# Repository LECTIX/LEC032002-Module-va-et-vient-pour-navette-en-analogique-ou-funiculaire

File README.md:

# LEC032002 - Module va et vient pour navette en analogique ou funiculaire
Fichiers sources pour le produit LEC032002

## Description du produit

- **AUTOMATIQUE** gérez votre train en mode navette ou votre funiculaire automatiquement
- **ACCÉLÉRATION** et freinage progressifs
- **TEMPORISATION** réglable entre 1 s et plus de 3 min
- **SIMPLICITÉ** Réglage facile de la vitesse maximum, du temps d'arrêt, de la courbe d'accélération et de freinage
- **SÉCURITÉ** Protection contre les courts circuits

## Utiliser les fichiers sources pour fabriquer le produit

Il n'est **pas nécessaire de savoir souder ou d'être bon en électronique** pour se procurer ce produit. Grâce aux fichiers sources publiés ici, vous pouvez être en mesure de faire fabriquer ce produit par un sous traitant.

**ATTENTION** ce produit nécessite une programmation afin de pouvoir fonctionner. Vous devez pour cela posséder le programmateur et programmer vous même la carte. Cette étape peut nécessiter des connaissances techniques, si nécessaire, nous vous encourrageons à vous rapprocher d'un club.

### Faire fabriquer chez un sous traitant

Il est aujourd'hui possible de faire fabriquer à moindre cout des cartes électroniques. Nous recommendons [JLCPCB](https://jlcpcb.com/) si vous voulez aller au moins cher. Si vous préférez un acteur européen, [eurocircuits](https://www.eurocircuits.com/) est un des acteurs reconnus.

1. Télécherger les sources de ce produit en cliquant sur le bouton `Code`, puis `Download ZIP`.
1. Décompresser le dossier.
1. Les fichiers pour la fabrication se trouvent dans le répertoire `hardware/prod`.
1. Se connecter sur [https://cart.jlcpcb.com/quote](https://cart.jlcpcb.com/quote)
1. Cliquer sur le bouton `Add gerber file` et sélectionner le fichier `gerbers.zip`.
1. Sélectionnez la quantité de cartes que vous souhaitez dans le champs `PCB Qty`.
1. Laisser toutes les autres options par défaut, puis cliquez sur le toggle switch en face de `PCB Assembly`, et enfin sur le bouton `confirm`.
1. Une preview de la carte électronique sans les composants doit apparaitre. Cliquez sur `NEXT`.
1. Cliquez sur le bouton `Add BOM File`, puis sélectionnez le fichier `bom.csv`
1. Cliquez sur le bouton `Add CPL File`, puis sélectionnez le fichier `pos.csv`
1. **Vérifier que tous les composants sont en stock** et bien sélectionnés, puis cliquez sur `NEXT`.
1. Une preview de la carte avec ses composants apparait. Continuer le chemin en cliquant sur `NEXT`.
1. Le prix final apparait. Sélectionnez la catégorie du produit, puis cliquez sur `SAVE TO CART`.
1. Une fois sauvegardé dans votre panier, vous pouvez valider votre commande et choisir le moyen d'acheminement. Afin de ne pas avoir à se préoccuper des frais de douane, nous vous conseillons de choisir une méthode d'expédition DDP.

Vous receverez vos cartes sous 1 à 3 semaines. 

**Nous ne sommes en aucun cas responsables des cartes qui arriveraient défectueuses ou non fonctionnelles.**

### Modifications des fichiers sources

Installez kicad 6 (ou version supérieure), et ouvrez le fichier LEC032002.kicad_pro

### Programation

Pour programmer le module, vous devez posséder
- un programmateur AVR type USBASP
- une sonde Tag-Connect TC2050

Le firmware se trouve dans le dossier du même nom. Il est recommandé d'utiliser VS-code et platform-io pour programmer la carte. Pour ce faire, branchez le programmateur à votre PC et à la carte à programmer, puis rentrer les commandes suivantes :

```
cd firmware
platformio run --target fuses && platformio run --target upload
```

### Regénérer les fichiers gerber, BOM, et position (Optionnel)

Peut se faire simplement en utilisant kikit :

```
cd hardware
docker run --rm -w /kikit -v $PWD:/kikit yaqwsx/kikit kikit fab jlcpcb --assembly --no-drc --schematic LEC032002.kicad_sch --field LCSC --corrections JLCPCB_CORRECTION --nametemplate LEC032002_{} LEC032002.kicad_pcb prod/

```
## Notices
[Manuel FR](docs/manual_fr.pdf)

## License
Tous nos fichiers sont plubliés sous les licenses
- CERN Open Hardware Licence Version 2 - Strongly Reciprocal pour ce qui touche au hardware
- GNU General Public License v3.0 pour tout ce qui est software

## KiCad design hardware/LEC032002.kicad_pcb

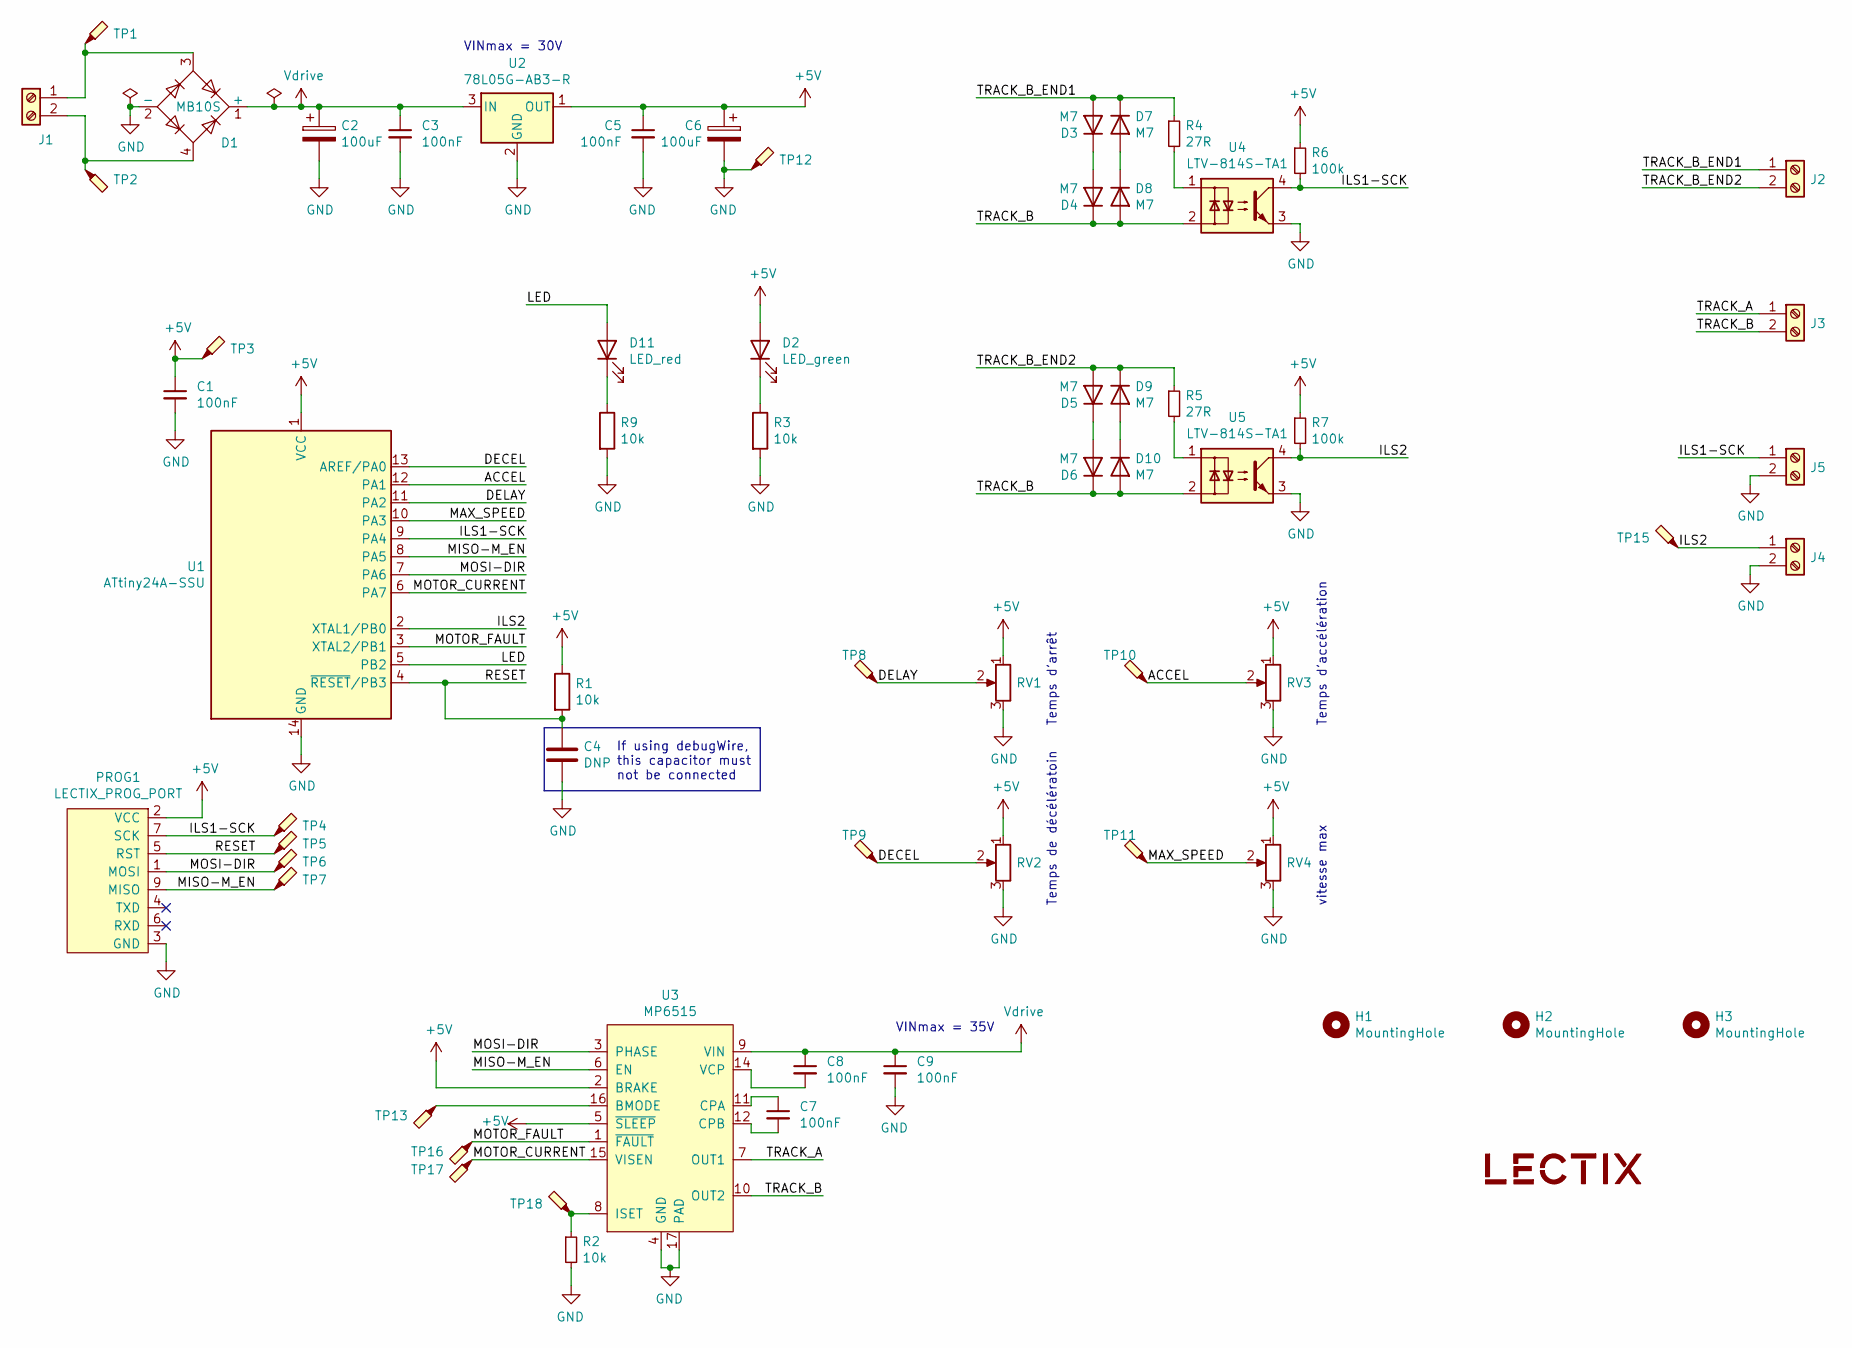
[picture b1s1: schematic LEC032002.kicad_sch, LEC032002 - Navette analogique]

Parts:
C1, C3, C5, C7, C8, C9: 100nF; C_0603_1608Metric; LCSC C14663
C2, C6: 100uF; CP_Elec_6.3x7.7; LCSC C249982
C4: DNP; C_0603_1608Metric; LCSC DNP
D1: MB10S; TO-269AA; LCSC C2488
D2: LED_green; LED_0603_1608Metric; MPN 19-217/GHC-YR1S2/3T; LCSC C72043
D3, D4, D5, D6, D7, D8, D9, D10: M7; D_SMA; MPN M7; LCSC C95872
D11: LED_red; LED_0603_1608Metric; LCSC C2286
H1, H2, H3: MountingHole; MountingHole_3.2mm_M3; LCSC DNP
J1: Screw_Terminal_01x02_green; TerminalBlock_bornier-2_P5.08mm-green; MPN DB126V-5.0-2P-GN; LCSC C395849
J2, J3, J4, J5: Screw_Terminal_01x02_blue; TerminalBlock_bornier-2_P5.08mm-blue; MPN DB301V-5.0-2P-BU-P; LCSC C430621
LOGO1: logo_lectix_25mm; Logo_10mm; LCSC DNP
PROG1: LECTIX_PROG_PORT; Tag-Connect_TC2050-IDC-FP_2x05_P1.27mm_Vertical; LCSC DNP
R1, R2, R3, R9: 10k; R_0603_1608Metric; LCSC C25804
R4, R5: 27R; R_0603_1608Metric; LCSC C25190
R6, R7: 100k; R_0603_1608Metric; LCSC C25803
RV1, RV2, RV3, RV4: pot_smd_100k_3362P; BOURNS-3362P_pot; MPN 3362P-1-104; LCSC C118966
TP1, TP2, TP3, TP4, TP5, TP6, TP7, TP8, TP9, TP10, TP11, TP12, TP13, TP15, TP16, TP17, TP18: TestPoint_Probe; TestPoint_Pad_D1.0mm; LCSC DNP
U1: ATtiny24A-SSU; SOIC-14_3.9x8.7mm_P1.27mm; LCSC C14909
U2: 78L05G-AB3-R; SOT-89-3; MPN 78L05G-AB3-R; LCSC C71136
U3: MP6515; HTSSOP-16-1EP_4.4x5mm_P0.65mm_EP3.4x5mm_Mask3x3mm_ThermalVi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; MPN MP6515GF-Z; LCSC C114139
U4, U5: LTV-814S-TA1; SMDIP-4_W9.53mm_Clearance8mm; MPN LTV-814S-TA1; LCSC C125118

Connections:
+5V: C1.1, C5.1, C6.1, D2.2 (A), PROG1.2 (VCC), R1.1, R6.1, R7.1, RV1.1, RV2.1, RV3.1, RV4.1, TP3.1, U1.1 (VCC), U2.1 (OUT), U3.2 (BRAKE), U3.5 (~SLEEP)
/ACCEL: RV3.2, TP10.1, U1.12 (PA1)
/DECEL: RV2.2, TP9.1, U1.13 (AREF/PA0)
/DELAY: RV1.2, TP8.1, U1.11 (PA2)
/ILS1-SCK: J5.1, PROG1.7 (SCK), R6.2, TP4.1, U1.9 (PA4), U4.4
/ILS2: J4.1, R7.2, TP15.1, U1.2 (XTAL1/PB0), U5.4
/LED: D11.2 (A), U1.5 (PB2)
/MAX_SPEED: RV4.2, TP11.1, U1.10 (PA3)
/MISO-M_EN: PROG1.9 (MISO), TP7.1, U1.8 (PA5), U3.6 (EN)
/MOSI-DIR: PROG1.1 (MOSI), TP6.1, U1.7 (PA6), U3.3 (PHASE)
/MOTOR_CURRENT: TP17.1, U1.6 (PA7), U3.15 (VISEN)
/MOTOR_FAULT: TP16.1, U1.3 (XTAL2/PB1), U3.1 (~FAULT)
/RESET: C4.1, PROG1.5 (RST), R1.2, TP5.1, U1.4 (~RESET/PB3)
/TRACK_A: J3.1, U3.7 (OUT1)
/TRACK_B: D4.1 (K), D6.1 (K), D8.2 (A), D10.2 (A), J3.2, U3.10 (OUT2), U4.2, U5.2
/TRACK_B_END1: D3.2 (A), D7.1 (K), J2.1, R4.1
/TRACK_B_END2: D5.2 (A), D9.1 (K), J2.2, R5.1
GND: C1.2, C2.2, C3.2, C4.2, C5.2, C6.2, C9.2, D1.2 (-), J4.2, J5.2, PROG1.3 (GND), PROG1.8 (GND), PROG1.10 (GND), R2.2, R3.2, R9.2, RV1.3, RV2.3, RV3.3, RV4.3, TP12.1, U1.14 (GND), U2.2 (GND), U3.4 (GND), U3.13 (GND), U3.17 (PAD), U4.3, U5.3
unnamed: C7.1, U3.11 (CPA)
unnamed: C7.2, U3.12 (CPB)
unnamed: C8.2, U3.14 (VCP)
unnamed: D1.3, J1.1, TP1.1
unnamed: D1.4, J1.2, TP2.1
unnamed: D2.1 (K), R3.1
unnamed: D3.1 (K), D4.2 (A)
unnamed: D5.1 (K), D6.2 (A)
unnamed: D7.2 (A), D8.1 (K)
unnamed: D9.2 (A), D10.1 (K)
unnamed: D11.1 (K), R9.1
unnamed: R2.1, TP18.1, U3.8 (ISET)
unnamed: R4.2, U4.1
unnamed: R5.2, U5.1
unnamed: TP13.1, U3.16 (BMODE)
Vdrive: C2.1, C3.1, C8.1, C9.1, D1.1 (+), U2.3 (IN), U3.9 (VIN)

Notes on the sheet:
VINmax = 35V
vitesse max
VINmax = 30V
Temps d’arrêt
If using debugWire, this capacitor must not be connected
Temps d’accélération
Temps de décélératoin

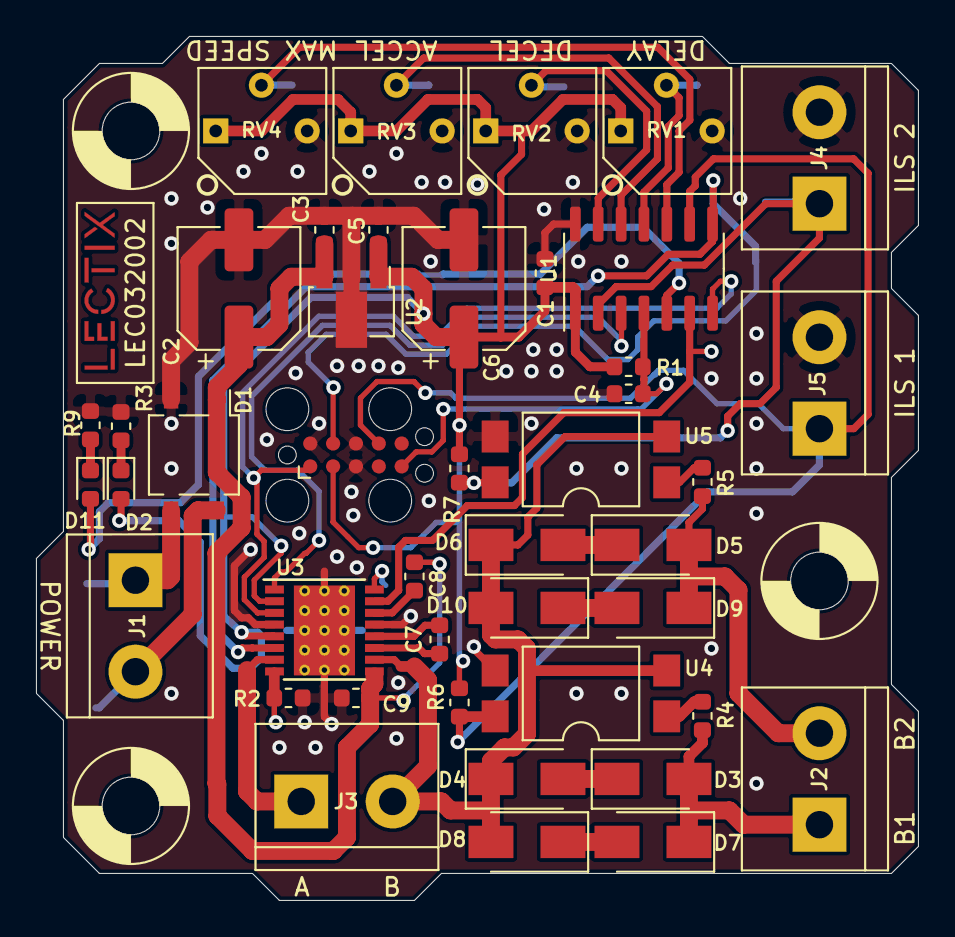
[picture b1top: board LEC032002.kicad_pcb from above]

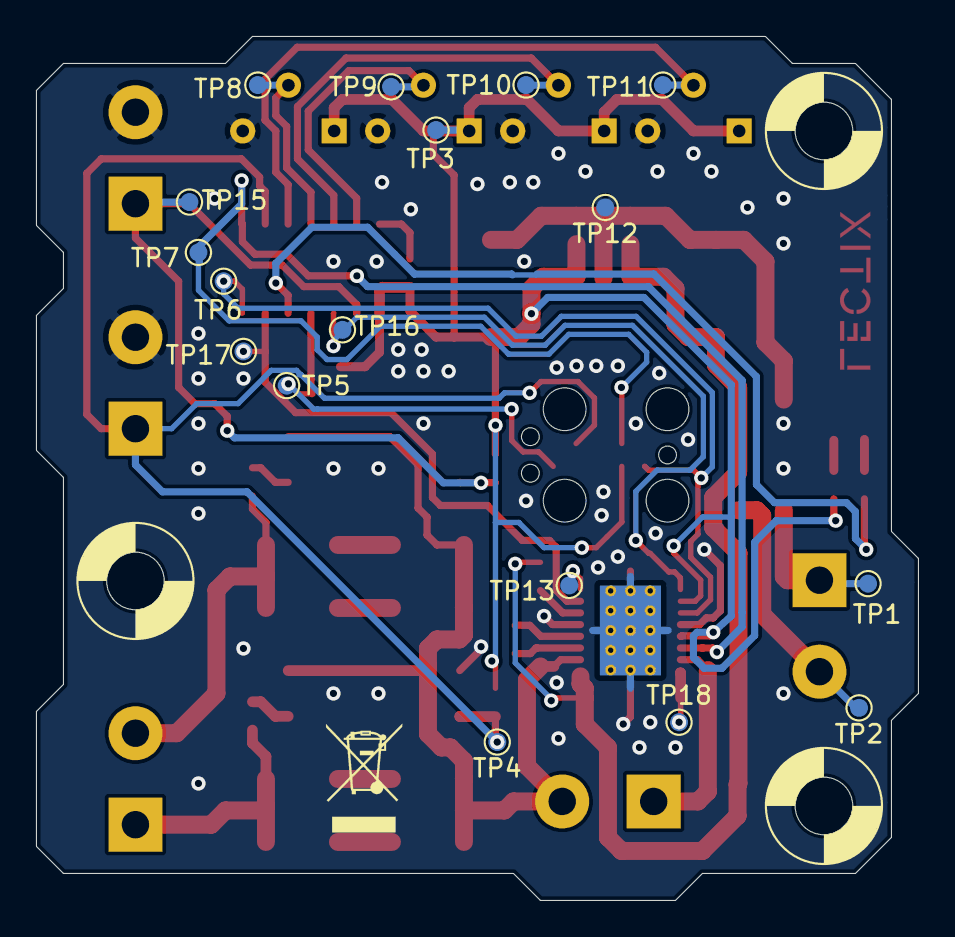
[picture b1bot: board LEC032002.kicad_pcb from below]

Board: 2 copper layers, 49.0 x 48.0 mm, 64 parts (17 on the bottom side), 34 nets.

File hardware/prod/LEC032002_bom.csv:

Comment,Designator,Footprint,LCSC
100nF,"C1,C3,C5,C7,C8,C9",Capacitor_SMD:C_0603_1608Metric,C14663
100uF,"C2,C6",Capacitor_SMD:CP_Elec_6.3x7.7,C249982
MB10S,D1,Package_TO_SOT_SMD:TO-269AA,C2488
LED_green,D2,LED_SMD:LED_0603_1608Metric,C72043
M7,"D3,D4,D5,D6,D7,D8,D9,D10",Diode_SMD:D_SMA,C95872
LED_red,D11,LED_SMD:LED_0603_1608Metric,C2286
Screw_Terminal_01x02_green,J1,0_connectors:TerminalBlock_bornier-2_P5.08mm-green,C395849
Screw_Terminal_01x02_blue,"J2,J3,J4,J5",0_connectors:TerminalBlock_bornier-2_P5.08mm-blue,C430621
10k,"R1,R2,R3,R9",Resistor_SMD:R_0603_1608Metric,C25804
27R,"R4,R5",Resistor_SMD:R_0603_1608Metric,C25190
100k,"R6,R7",Resistor_SMD:R_0603_1608Metric,C25803
pot_smd_100k_3362P,"RV1,RV2,RV3,RV4",0_potentiometers:BOURNS-3362P_pot,C118966
ATtiny24A-SSU,U1,Package_SO:SOIC-14_3.9x8.7mm_P1.27mm,C14909
78L05G-AB3-R,U2,Package_TO_SOT_SMD:SOT-89-3,C71136
MP6515,U3,Package_SO:HTSSOP-16-1EP_4.4x5mm_P0.65mm_EP3.4x5mm_Mask3x3mm_ThermalVias,C114139
LTV-814S-TA1,"U4,U5",Package_DIP:SMDIP-4_W9.53mm_Clearance8mm,C125118

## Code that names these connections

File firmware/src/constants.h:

#ifndef CONSTANTS_H
#define CONSTANTS_H

/**
 * PB0  0       PCINT8  XTAL1
 * PB1  1       PCINT9  XTAL2
 * PB3  11      PCINT11 RESET
 * PB2  2       PCINT10 OC0A    INT0
 * PA7  3   A7  PCINT7  OC0B
 * PA6  4   A6  PCINT6  MOSI    DI  SDA OC1A
 * PA5  5   A5  PCINT5  MISO    DO  OC1B
 * PA4  6   A4  PCINT4  SCK     SCL 
 * PA3  7   A3  PCINT3
 * PA2  8   A2  PCINT2  AIN1
 * PA1  9   A1  PCINT1  AIN0
 * PA0  10  A0  PCINT0  AREF
 */ 


#define PIN_DECEL A0
#define PIN_ACCEL A1
#define PIN_DELAY A2
#define PIN_MAX_SPEED A3
#define PIN_ILS1 6
#define PIN_MOTOR_EN 5
#define PIN_MOTOR_DIR 4
#define PIN_MOTOR_CURRENT A7
#define PIN_ILS2 0
#define PIN_MOTOR_FAULT 1
#define PIN_LED 2

// Constants

#define DEFAULT_ACCELERATION 5
#define DEFAULT_DECELERATION 5
#define DEFAULT_MAX_SPEED 255
#define MIN_MAXIMUM_SPEED 50

#define FORWARD_DIR 0
#define BACKWARD_DIR 1

#endif

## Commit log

2023-04-19 Add hardware source files
2023-04-19 Fix part placement
2023-04-19 Add firmware and basic programming instructions
2023-04-19 Add firmware License
